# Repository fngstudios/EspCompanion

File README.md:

# EspCompanion

Esp8266 + Atmega328 dev board.
Discontinued project, with Esp32 its no longer needed.

## Features  

Esp8266 and Atmega328 share the i2c bus, Esp is the master and the mega acts as a i/o
expander, with adc,pwm,serial and other libraries support.
With custom i2c library the Esp can initialize any library on the mega and it will run 
in the background untill the esp request data or sends data.

## Images

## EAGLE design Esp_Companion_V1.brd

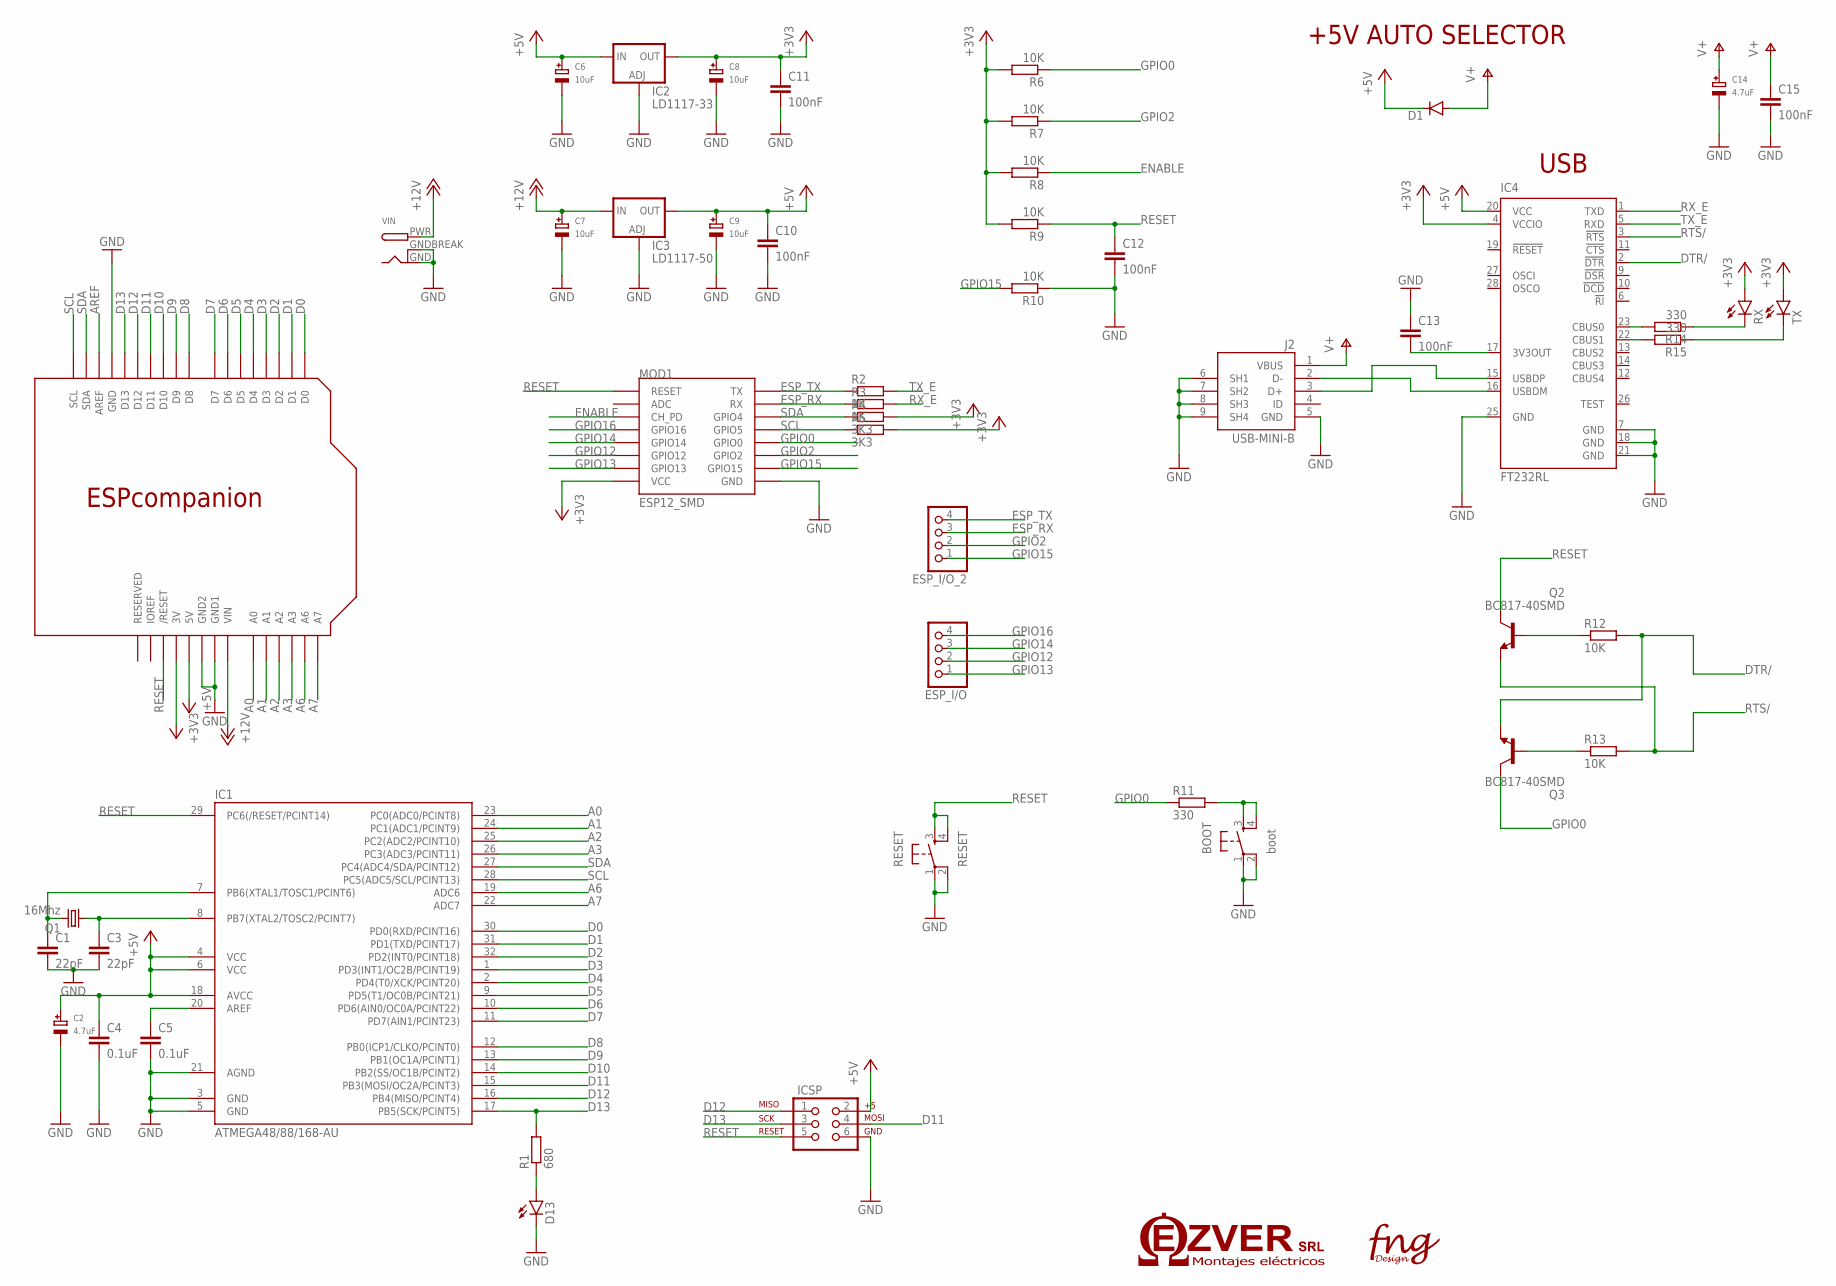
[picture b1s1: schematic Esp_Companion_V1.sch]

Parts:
BOOT: boot; TACTILE-PTH
C1, C3: 22pF; C0603
C2, C14: 4.7uF; EIA3216-18/A-R
C4, C5: 0.1uF; C0603
C6, C7, C8, C9: 10uF; EIA3216-18/A-R
C10, C11, C12, C13, C15: 100nF; C0603
D1: DIODESMA-ALT; SMA-DIODE_ALT
D13: LED-FKIT-1206; FKIT-LED-1206
ESP_I/O: PINHD-1X4; 1X04
ESP_I/O_2: PINHD-1X4; 1X04
IC1: ATMEGA48/88/168-AU; TQFP32-08
IC2: LD1117-33; DPACK
IC3: LD1117-50; DPACK
IC4: FT232RL; SSOP28
ICSP: AVR_SPI_PRG_62X3_LOCK; 2X3_LOCK
J2: USB-MINI-B
LAY1: ESPCOMPANIONHOLES; ESPCOMPANION_HOLES
MOD1: ESP12_SMD
Q1: 16Mhz; HC49U70
Q2, Q3: BC817-40SMD; SOT23-BEC
R1: 680; R0603
R2, R3: 1K; R0603
R4, R5: 3K3; R0603
R6, R7, R8, R9, R10, R12, R13: 10K; R0603
R11, R14, R15: 330; R0603
RESET: RESET; TACTILE-PTH
RX: LED-FKIT-1206; FKIT-LED-1206
TX: LED-FKIT-1206; FKIT-LED-1206
VIN: DCBARRELPTH; DCJACK_2MM_PTH

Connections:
+3V3: C8.+, C11.1, IC2.4 (OUT), IC4.4 (VCCIO), LAY1.3V, MOD1.P$8 (VCC), R4.2, R5.2, R6.2, R7.2, R8.2, R9.2, RX.A, TX.A
+5V: C2.+, C4.1, C6.+, C9.+, C10.1, D1.C, IC1.4 (VCC), IC1.6 (VCC), IC1.18 (AVCC), IC2.3 (IN), IC3.4 (OUT), IC4.20 (VCC), ICSP.2, LAY1.5V
+12V: C7.+, IC3.3 (IN), LAY1.VIN, VIN.PWR
A0: IC1.23 (PC0(ADC0/PCINT8)), LAY1.A0
A1: IC1.24 (PC1(ADC1/PCINT9)), LAY1.A1
A2: IC1.25 (PC2(ADC2/PCINT10)), LAY1.A2
A3: IC1.26 (PC3(ADC3/PCINT11)), LAY1.A3
A6: IC1.19 (ADC6), LAY1.A6
A7: IC1.22 (ADC7), LAY1.A7
AREF: LAY1.AREF
D0: IC1.30 (PD0(RXD/PCINT16)), LAY1.D0
D1: IC1.31 (PD1(TXD/PCINT17)), LAY1.D1
D2: IC1.32 (PD2(INT0/PCINT18)), LAY1.D2
D3: IC1.1 (PD3(INT1/OC2B/PCINT19)), LAY1.D3
D4: IC1.2 (PD4(T0/XCK/PCINT20)), LAY1.D4
D5: IC1.9 (PD5(T1/OC0B/PCINT21)), LAY1.D5
D6: IC1.10 (PD6(AIN0/OC0A/PCINT22)), LAY1.D6
D7: IC1.11 (PD7(AIN1/PCINT23)), LAY1.D7
D8: IC1.12 (PB0(ICP1/CLKO/PCINT0)), LAY1.D8
D9: IC1.13 (PB1(OC1A/PCINT1)), LAY1.D9
D10: IC1.14 (PB2(SS/OC1B/PCINT2)), LAY1.D10
D11: IC1.15 (PB3(MOSI/OC2A/PCINT3)), ICSP.4, LAY1.D11
D12: IC1.16 (PB4(MISO/PCINT4)), ICSP.1, LAY1.D12
D13: IC1.17 (PB5(SCK/PCINT5)), ICSP.3, LAY1.D13, R1.2
DTR/: IC4.2 (!DTR), Q3.E, R12.2
ENABLE: MOD1.P$3 (CH_PD), R8.1
ESP_RX: ESP_I/O_2.3, MOD1.P$15 (RX), R3.1
ESP_TX: ESP_I/O_2.4, MOD1.P$16 (TX), R2.1
GND: BOOT.1, BOOT.2, C1.2, C2.-, C3.2, C4.2, C5.2, C6.-, C7.-, C8.-, C9.-, C10.2, C11.2, C12.2, C13.1, C14.-, C15.2, D13.C, IC1.3 (GND), IC1.5 (GND), IC1.21 (AGND), IC2.1 (ADJ), IC3.1 (ADJ), IC4.7 (GND), IC4.18 (GND), IC4.21 (GND), IC4.25 (GND), ICSP.6, J2.5 (GND), J2.6 (SH1), J2.7 (SH2), J2.8 (SH3), J2.9 (SH4), LAY1.GND, LAY1.GND1, LAY1.GND2, MOD1.P$9 (GND), R10.1, RESET.1, RESET.2, VIN.GND, VIN.GNDBREAK
GPIO0: MOD1.P$12 (GPIO0), Q3.C, R6.1, R11.1
GPIO2: ESP_I/O_2.2, MOD1.P$11 (GPIO2), R7.1
GPIO12: ESP_I/O.2, MOD1.P$6 (GPIO12)
GPIO13: ESP_I/O.1, MOD1.P$7 (GPIO13)
GPIO14: ESP_I/O.3, MOD1.P$5 (GPIO14)
GPIO15: ESP_I/O_2.1, MOD1.P$10 (GPIO15), R10.2
GPIO16: ESP_I/O.4, MOD1.P$4 (GPIO16)
unnamed: D13.A, R1.1
unnamed: BOOT.3, BOOT.4, R11.2
unnamed: Q2.B, R12.1
unnamed: Q3.B, R13.1
unnamed: C3.1, IC1.8 (PB7(XTAL2/TOSC2/PCINT7)), Q1.1
unnamed: C1.1, IC1.7 (PB6(XTAL1/TOSC1/PCINT6)), Q1.2
unnamed: C5.1, IC1.20 (AREF)
unnamed: C13.2, IC4.17 (3V3OUT)
unnamed: IC4.23 (CBUS0), R14.2
unnamed: IC4.22 (CBUS1), R15.2
unnamed: R15.1, TX.C
unnamed: R14.1, RX.C
unnamed: IC4.16 (USBDM), J2.2 (D-)
unnamed: IC4.15 (USBDP), J2.3 (D+)
RESET: C12.1, IC1.29 (PC6(/RESET/PCINT14)), ICSP.5, LAY1.RESET (/RESET), MOD1.P$1 (RESET), Q2.C, R9.1, RESET.3, RESET.4
RTS/: IC4.3 (!RTS), Q2.E, R13.2
RX_E: IC4.1 (TXD), R3.2
SCL: IC1.28 (PC5(ADC5/SCL/PCINT13)), LAY1.SCL, MOD1.P$14 (GPIO5), R5.1
SDA: IC1.27 (PC4(ADC4/SDA/PCINT12)), LAY1.SDA, MOD1.P$13 (GPIO4), R4.1
TX_E: IC4.5 (RXD), R2.2
V+: C14.+, C15.1, D1.A, J2.1 (VBUS)

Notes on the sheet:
USB
+5V AUTO SELECTOR

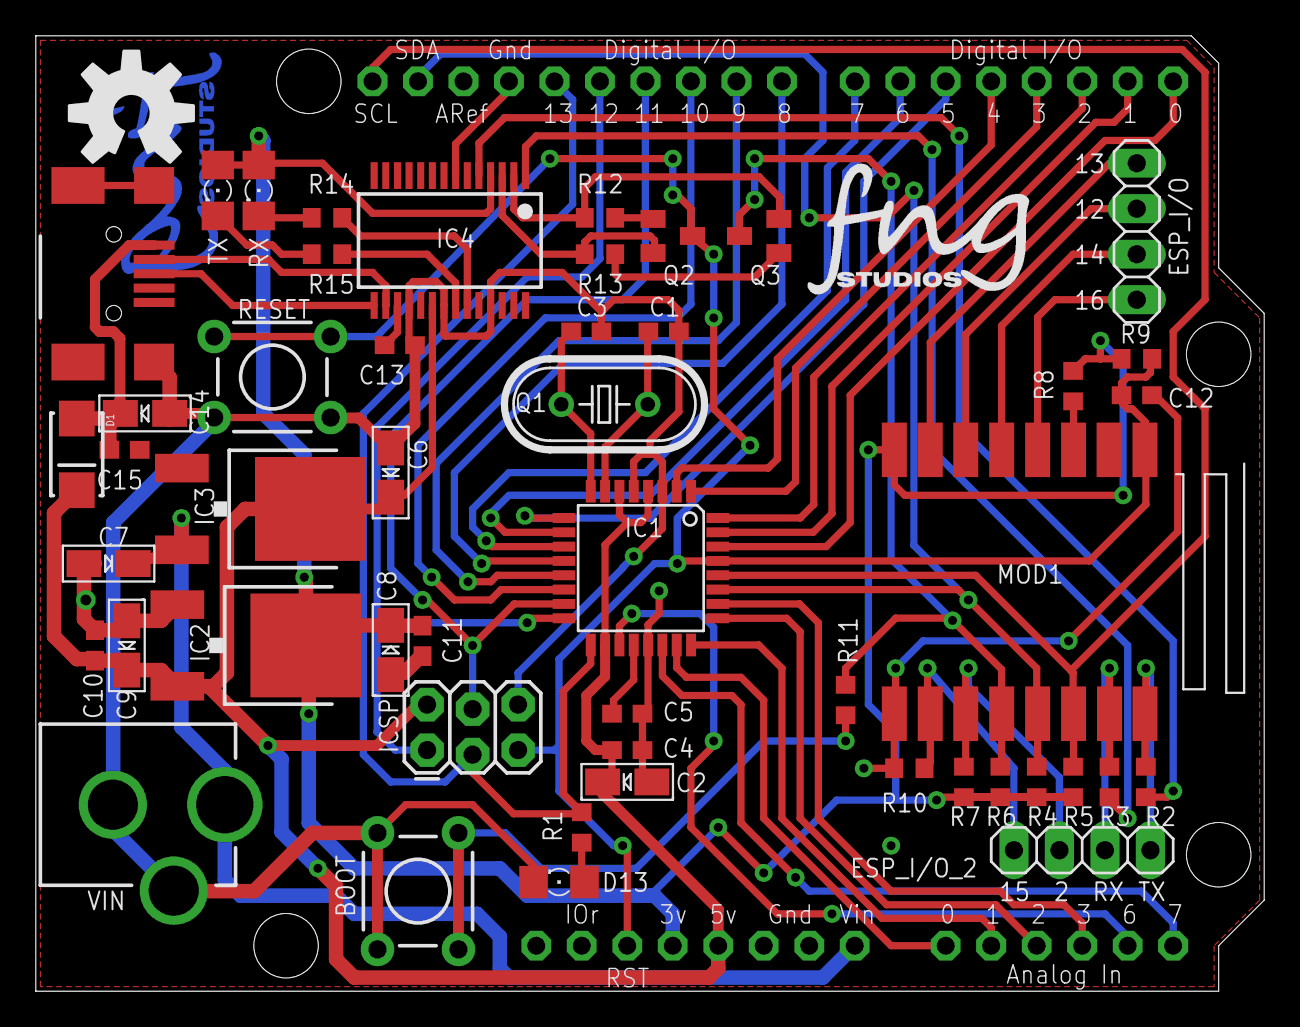
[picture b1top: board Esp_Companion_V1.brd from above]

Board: 2 copper layers, 68.6 x 53.3 mm, 53 parts (1 on the bottom side), 56 nets.

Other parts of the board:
U$2: LOGOFNGNAME1
U$3: LOGOFNG
U$4: OSHW-LOGO-L

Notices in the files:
parts and their libraries:
SparkFun-Electromechanical: Licensing: CC v3.0 Share-Alike You are welcome to use this library for commercial purposes.
SparkFun-LED: Licensing: Creative Commons ShareAlike 4.0 International - https://creativecommons.org/licenses/by-sa/4.0
